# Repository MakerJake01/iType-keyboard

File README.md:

# iType-keyboard-
A keyboard I made that uses a pro mciro. 
It uses 17 BAV70 didoes and 32 MX switches. 
There are some M2 mouting points that chould work for tray mount. 
This board is untested but maybe it would work. 

I made the pcb but Dr. Ratsby made the KLE.

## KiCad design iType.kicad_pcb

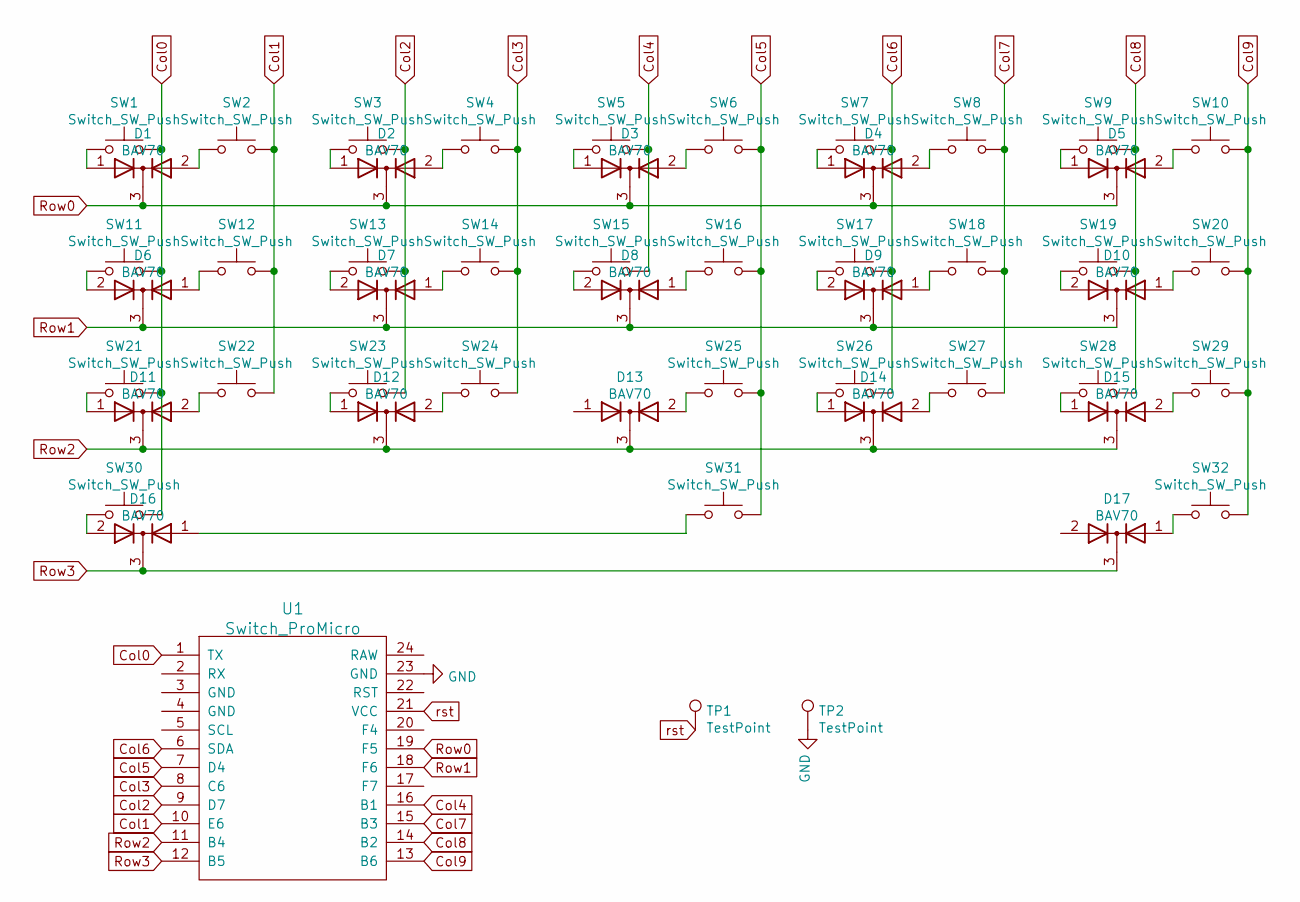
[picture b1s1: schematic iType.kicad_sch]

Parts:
D1, D2, D3, D4, D5, D6, D7, D8, D9, D10, D11, D12, D13, D14, D15, D16, D17: BAV70; SOT-23
SW1, SW2, SW3, SW4, SW5, SW6, SW7, SW8, SW9, SW10, SW11, SW12, SW13, SW14, SW15, SW16, SW17, SW18, SW19, SW20, SW22, SW23, SW24, SW25, SW26, SW27, SW28: Switch_SW_Push; SW_Cherry_MX_1.00u_PCB
SW21, SW29: Switch_SW_Push; SW_Cherry_MX_1.50u_PCB
SW30, SW32: Switch_SW_Push; SW_Cherry_MX_1.75u_PCB
SW31: Switch_SW_Push; SW_Cherry_MX_6.25u_PCB
TP1, TP2: TestPoint; TestPoint_Pad_1.5x1.5mm
U1: Switch_ProMicro; ArduinoProMicro

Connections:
Col0: SW1.2, SW11.2, SW21.2, SW30.2, U1.1 (TX)
Col1: SW2.2, SW12.2, SW22.2, U1.10 (E6)
Col2: SW3.2, SW13.2, SW23.2, U1.9 (D7)
Col3: SW4.2, SW14.2, SW24.2, U1.8 (C6)
Col4: SW5.2, SW15.2, U1.16 (B1)
Col5: SW6.2, SW16.2, SW25.2, SW31.2, U1.7 (D4)
Col6: SW7.2, SW17.2, SW26.2, U1.6 (SDA)
Col7: SW8.2, SW18.2, SW27.2, U1.15 (B3)
Col8: SW9.2, SW19.2, SW28.2, U1.14 (B2)
Col9: SW10.2, SW20.2, SW29.2, SW32.2, U1.13 (B6)
GND: TP2.1, U1.23 (GND); also elsewhere on the board
unnamed: D1.1 (A), SW1.1
unnamed: D1.2 (A), SW2.1
unnamed: D2.1 (A), SW3.1
unnamed: D2.2 (A), SW4.1
unnamed: D3.1 (A), SW5.1
unnamed: D3.2 (A), SW6.1
unnamed: D4.1 (A), SW7.1
unnamed: D4.2 (A), SW8.1
unnamed: D5.1 (A), SW9.1
unnamed: D5.2 (A), SW10.1
unnamed: D6.1 (A), SW12.1
unnamed: D6.2 (A), SW11.1
unnamed: D11.1 (A), SW21.1
unnamed: D11.2 (A), SW22.1
unnamed: D12.1 (A), SW23.1
unnamed: D12.2 (A), SW24.1
unnamed: D13.2 (A), SW25.1
unnamed: D14.1 (A), SW26.1
unnamed: D14.2 (A), SW27.1
unnamed: D15.1 (A), SW28.1
unnamed: D15.2 (A), SW29.1
unnamed: D7.2 (A), SW13.1
unnamed: D7.1 (A), SW14.1
unnamed: D8.2 (A), SW15.1
unnamed: D8.1 (A), SW16.1
unnamed: D9.2 (A), SW17.1
unnamed: D9.1 (A), SW18.1
unnamed: D10.2 (A), SW19.1
unnamed: D10.1 (A), SW20.1
unnamed: D16.2 (A), SW30.1
unnamed: D16.1 (A), SW31.1
unnamed: D17.1 (A), SW32.1
Row0: D1.3 (K), D2.3 (K), D3.3 (K), D4.3 (K), D5.3 (K), U1.19 (F5)
Row1: D6.3 (K), D7.3 (K), D8.3 (K), D9.3 (K), D10.3 (K), U1.18 (F6)
Row2: D11.3 (K), D12.3 (K), D13.3 (K), D14.3 (K), D15.3 (K), U1.11 (B4)
Row3: D16.3 (K), D17.3 (K), U1.12 (B5)
rst: TP1.1, U1.21 (VCC); also elsewhere on the board

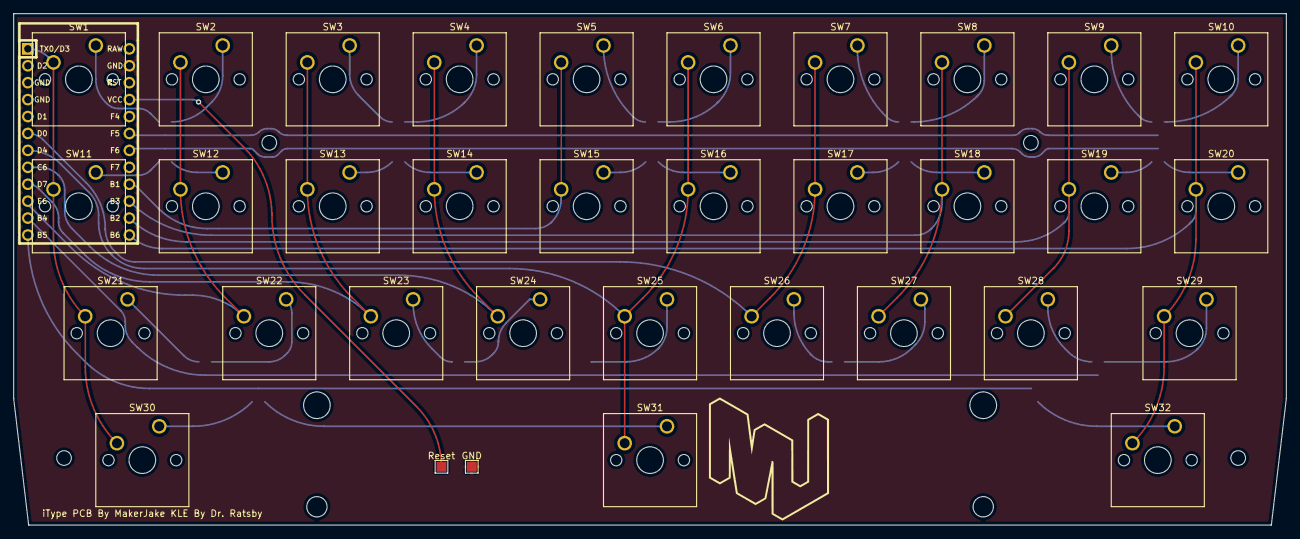
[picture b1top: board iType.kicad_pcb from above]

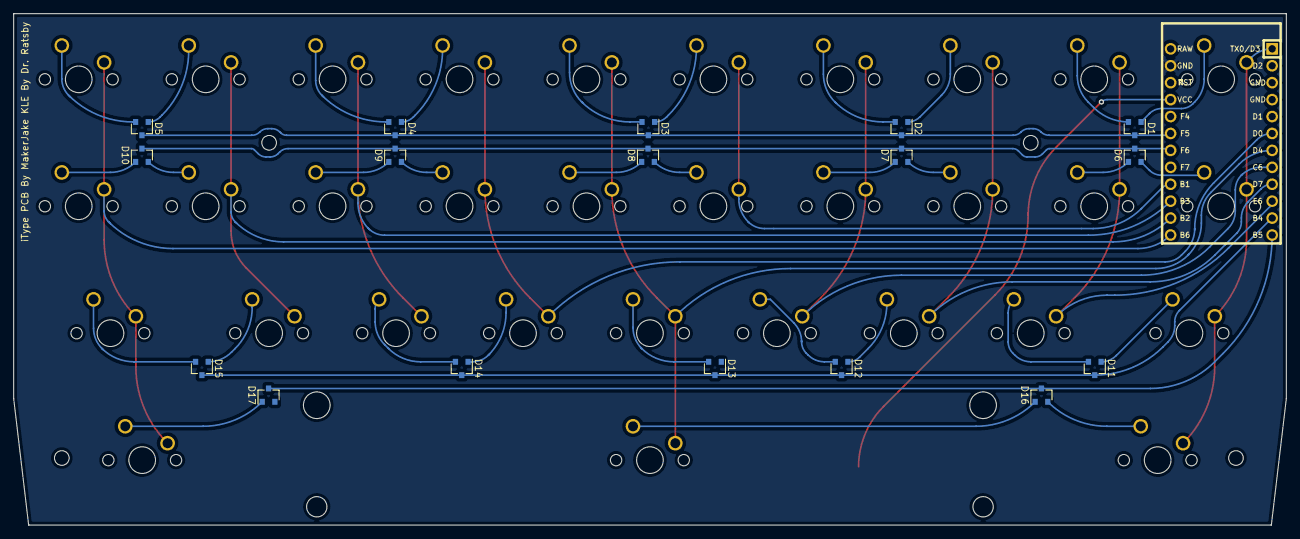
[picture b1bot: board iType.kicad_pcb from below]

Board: 2 copper layers, 191.0 x 76.8 mm, 52 parts (17 on the bottom side), 48 nets.

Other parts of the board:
GND: TestPoint; TestPoint_Pad_1.5x1.5mm
Reset: TestPoint; TestPoint_Pad_1.5x1.5mm

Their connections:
GND: GND.1; also elsewhere on the board
rst: Reset.1; also elsewhere on the board

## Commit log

2022-01-08 Add files via upload
    all the fun files
